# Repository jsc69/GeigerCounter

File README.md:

# GeigerCounter
Geiger counter for the Brutzelboy

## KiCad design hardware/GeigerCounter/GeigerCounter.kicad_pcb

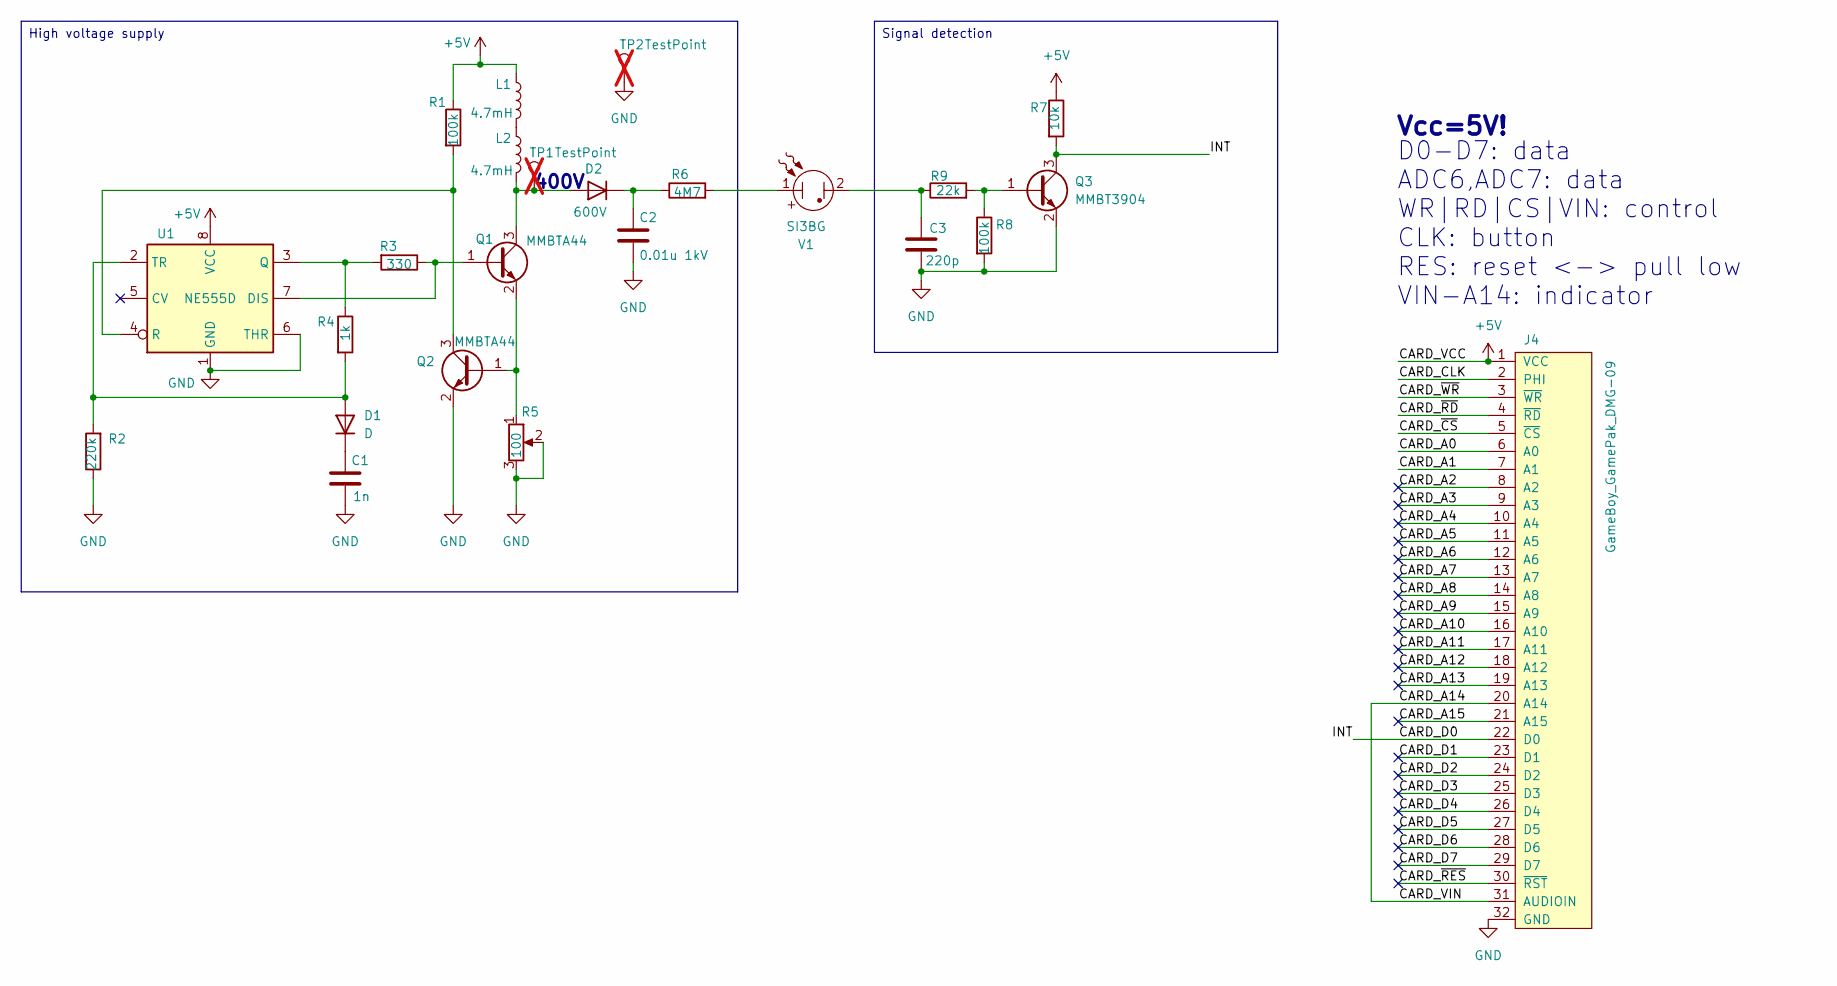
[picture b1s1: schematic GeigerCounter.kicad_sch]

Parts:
C1: 1n; C_0805_2012Metric_Pad1.18x1.45mm_HandSolder
C2: 0.01u 1kV; C_1206_3216Metric_Pad1.33x1.80mm_HandSolder
C3: 220p; C_0805_2012Metric_Pad1.18x1.45mm_HandSolder
D1: D; D_0805_2012Metric_Pad1.15x1.40mm_HandSolder
D2: 600V; D_SOD-123F
J4: GameBoy_GamePak_DMG-09; Gameboy-Connector
L1, L2: 4.7mH; IND-SMD_L6.6-W4.4; LCSC C168108
Q1, Q2: MMBTA44; SOT-23
Q3: MMBT3904; SOT-23
R1, R8: 100k; R_0805_2012Metric_Pad1.20x1.40mm_HandSolder
R2: 220k; R_0805_2012Metric_Pad1.20x1.40mm_HandSolder
R3: 330; R_0805_2012Metric_Pad1.20x1.40mm_HandSolder
R4: 1k; R_0805_2012Metric_Pad1.20x1.40mm_HandSolder
R5: 100; Potentiometer_Bourns_TC33X_Vertical
R6: 4M7; R_2010_5025Metric_Pad1.40x2.65mm_HandSolder; LCSC C2765816
R7: 10k; R_0805_2012Metric_Pad1.20x1.40mm_HandSolder
R9: 22k; R_0805_2012Metric_Pad1.20x1.40mm_HandSolder
TP1, TP2: TestPoint; PinSocket_1x01_P2.54mm_Vertical; not fitted
U1: NE555D; SOIC-8_3.9x4.9mm_P1.27mm
V1: SI3BG

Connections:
+5V: J4.1 (VCC), L1.1, R1.1, R7.1, U1.8 (VCC)
/CARD_A0: J4.6 (A0)
/CARD_A1: J4.7 (A1)
/CARD_A2: J4.8 (A2)
/CARD_A3: J4.9 (A3)
/CARD_A4: J4.10 (A4)
/CARD_A5: J4.11 (A5)
/CARD_A6: J4.12 (A6)
/CARD_A7: J4.13 (A7)
/CARD_A8: J4.14 (A8)
/CARD_A9: J4.15 (A9)
/CARD_A10: J4.16 (A10)
/CARD_A11: J4.17 (A11)
/CARD_A12: J4.18 (A12)
/CARD_A13: J4.19 (A13)
/CARD_A14: J4.20 (A14), J4.31 (AUDIOIN)
/CARD_A15: J4.21 (A15)
/CARD_CLK: J4.2 (PHI)
/CARD_D0: J4.22 (D0), Q3.3 (C), R7.2
/CARD_D1: J4.23 (D1)
/CARD_D2: J4.24 (D2)
/CARD_D3: J4.25 (D3)
/CARD_D4: J4.26 (D4)
/CARD_D5: J4.27 (D5)
/CARD_D6: J4.28 (D6)
/CARD_D7: J4.29 (D7)
/CARD_~CS: J4.5 (~CS)
/CARD_~RD: J4.4 (~RD)
/CARD_~RES: J4.30 (~RST)
/CARD_~WR: J4.3 (~WR)
GND: C1.2, C2.2, C3.2, J4.32 (GND), Q2.2 (E), Q3.2 (E), R2.1, R5.2, R5.3, R8.2, TP2.1, U1.1 (GND), U1.6 (THR)
unnamed: C3.1, R9.1, V1.2
unnamed: D1.2 (A), R2.2, R4.2, U1.2 (TR)
unnamed: C1.1, D1.1 (K)
unnamed: D2.2 (A), L2.2, Q1.3 (C), TP1.1
unnamed: C2.1, D2.1 (K), R6.1
unnamed: L1.2, L2.1
unnamed: Q1.1 (B), R3.1, U1.7 (DIS)
unnamed: Q1.2 (E), Q2.1 (B), R5.1
unnamed: Q2.3 (C), R1.2, U1.4 (R)
unnamed: Q3.1 (B), R8.1, R9.2
unnamed: R6.2, V1.1
unnamed: R3.2, R4.1, U1.3 (Q)

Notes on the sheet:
Vcc=5V!
400V
D0-D7: data ADC6,ADC7: data WR|RD|CS|VIN: control CLK: button RES: reset <-> pull low VIN-A14: indicator
High voltage supply
Signal detection

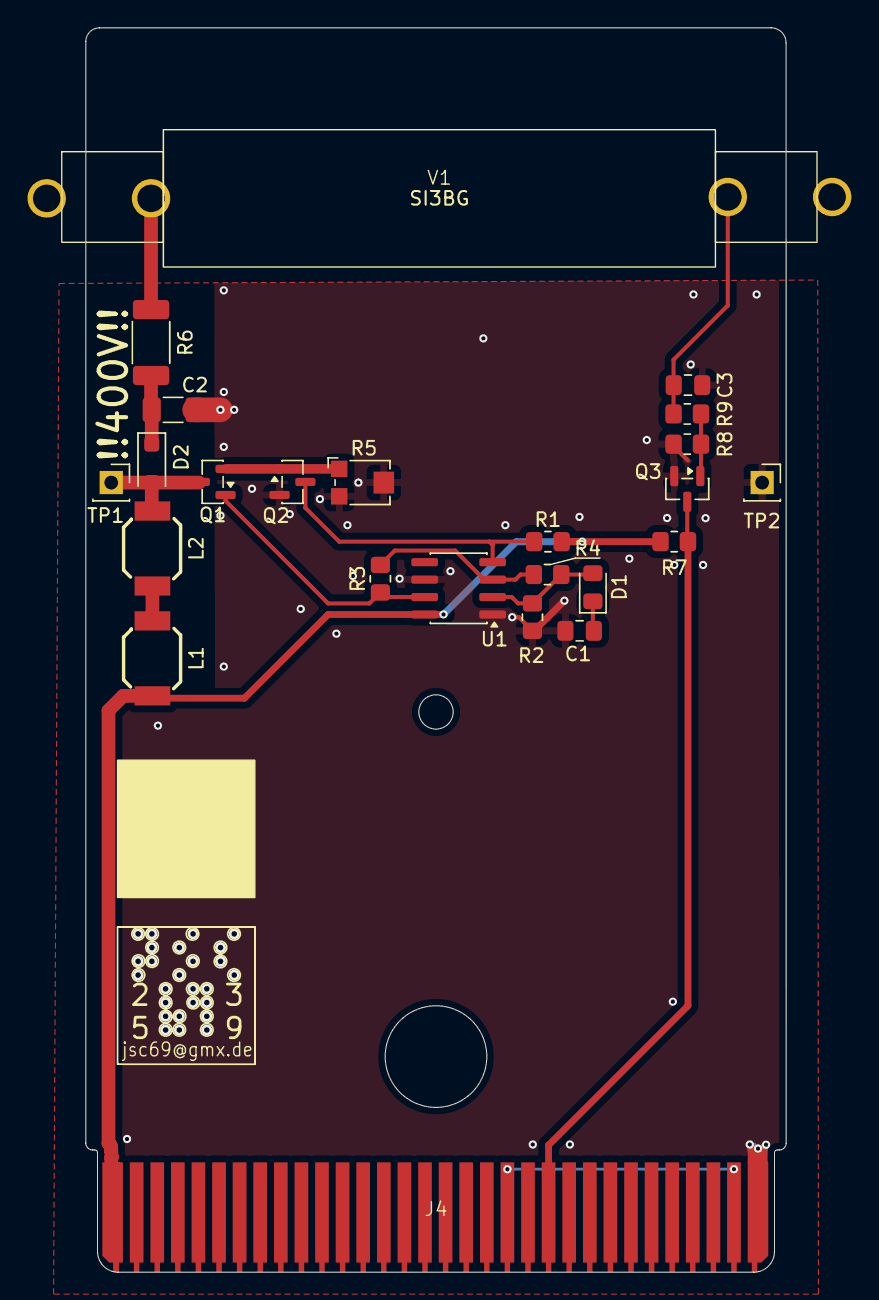
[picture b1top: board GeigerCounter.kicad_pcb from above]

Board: 2 copper layers, 51.0 x 90.6 mm, 24 parts (0 on the bottom side), 16 nets.

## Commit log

2025-10-31 init
2025-11-01 start kicad
2025-11-01 remove backups
2025-11-02 work with kicad
2026-01-06 change to 2 inductors
